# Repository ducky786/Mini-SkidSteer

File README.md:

# DESK TOP SKIDSTEER

My project is a small RC skidsteer for the desktop to cure bordom. This Skidsteer is around 80mm x 70mm with a arm that includes a bucket tilt. The arm and the Tilt are powered by servos while the drive bace is powered by 2 N20 motors. The 
I wanted to build this beucase I found an intrest in these small desktop toys that could be fun to kill time on your desk. I went for a skidsteer because it would consist of something more then just simply driving around on top of your desk.  Like picking up small
things and throwing them around. Another reason I wanted to build this was beucase I also wanted to learn something new! During this build I have defenetly learn a significant amound of cad and PCB design! But the main reason is to have pure fun with a mini constuction vehicel!! 
# CAD:

The wheels are place holders for a 26mm D-ring Wheels: [Wheels](https://www.amazon.com/10pcs-D-Hole-Rubber-Wheel-Suitable/dp/B0DHS12GDV/ref=sr_1_3?crid=JYD2UDDS1NEK&dib=eyJ2IjoiMSJ9.ZUXECa4swdUpnlJCNFAChQdrSCF2_hyKX8ZRQ2ua2YUncgO5PiK5-fhxESZpHSc04xRms3dZP7bGo22MBXnhl2GiFjDrSeCp869mCpt2dDXZk3buzny7Sudp0jAhjKUcEA7j7tARDvNgPD-RxQ5BFpu_E_WtRcR4WOEt8GHUK6RN7SL4UtHEZsm3R7V5XJPagJUR_B_1uT-b5DjtV5n_0yKpyzRRbffM9ZdXg7WJBNcLcRB7_FF1wIvSGdpv8AstDdXbFSEhfm7NKxJSys81x3GqS7OE68Zp1z-JxQ1wk4M.ZB2Gj1L4j-ghlaeTYDEn---1bgTsKAoD6mUg0iyUQDg&dib_tag=se&keywords=n20+motor+wheels&qid=1753996532&sprefix=n20+motor+wheels%2Caps%2C124&sr=8-3)

# PCB:

# Wire-ring Diagram:

# FIRMWARE:

# BOM:

| Part              | Quantity        | Price  | Link                                                                                                                                                                                                                                                                                                                                                                                                                                                                                                                                                                                             |
|-------------------|-----------------|--------|--------------------------------------------------------------------------------------------------------------------------------------------------------------------------------------------------------------------------------------------------------------------------------------------------------------------------------------------------------------------------------------------------------------------------------------------------------------------------------------------------------------------------------------------------------------------------------------------------|
| N20 Motors        | 2(comes with 3) | $9.99  | https://www.amazon.com/Acxico-Micro-Motor-3V-6V-Gearbox/dp/B09DG3GCGK/ref=sr_1_6?crid=2OI8KQ857NSB1&dib=eyJ2IjoiMSJ9.PkC4L7juc7TBvok5GyDdI7hLUVsyJ1bXnRvRXlihFuC0tuFr0EGfKIyFzPnAN5yKceG9SoHprCtbqYV4n7I_Zr-v1A3x4khd6QiGyFw154ci5AssINA13NQLaWW2FqRzkFSk5cMwQ_EzwAtZCdI4P1ZcjGlnBcWYDLRE6otBmBDZr-u-BCU8r-wDdhpqUWX1Tu8i0kttiPHRSya24dCC48jhBziSzb0c3fjVY09DPHAQZ82jpYmAuD5ZZlAhsl23H0OCtbkOdgwN9skI81BPHVLWugW-Nfu1aNeGGhEbY2A.YVqZWv7cAqLJMA5_e4uScZz4QUkldOzOEJFcsFCGGJc&dib_tag=se&keywords=N20+motors&qid=1753995893&sprefix=n20+motors%2Caps%2C137&sr=8-6                                 |
| Buck Converter    | 1               | $1.33  | https://www.aliexpress.us/item/3256809224651081.html?spm=a2g0o.productlist.main.4.51657788dJtPVx&aem_p4p_detail=202507291440413645293400774410000784233&algo_pvid=df29eea6-074c-4400-bbc7-bf50f68b366f&algo_exp_id=df29eea6-074c-4400-bbc7-bf50f68b366f-3&pdp_ext_f=%7B%22order%22%3A%228%22%2C%22eval%22%3A%221%22%7D&pdp_npi=4%40dis%21USD%211.33%210.77%21%21%211.33%210.77%21%402103245417538252412368642e00ae%2112000049015556004%21sea%21US%216238534509%21X&curPageLogUid=JzbwaxZXZo7C&utparam-url=scene%3Asearch%7Cquery_from%3A&search_p4p_id=202507291440413645293400774410000784233_1 |
| DRV8833           | 1               | $2.24  | https://www.aliexpress.us/item/3256806906685301.html?spm=a2g0o.productlist.main.4.6ea27fc4uwtPAg&aem_p4p_detail=2025073114100314644857276615300003037063&algo_pvid=8cc3c05c-6c7b-45dc-bfae-e0f3d2b46d45&algo_exp_id=8cc3c05c-6c7b-45dc-bfae-e0f3d2b46d45-3&pdp_ext_f=%7B"order"%3A"12"%2C"eval"%3A"1"%7D&pdp_npi=4%40dis%21USD%215.74%212.24%21%21%2141.08%2116.03%21%402103244617539962038712743e4150%2112000039378712005%21sea%21US%216395794669%21X&curPageLogUid=tkZwLZppvI4E&utparam-url=scene%3Asearch%7Cquery_from%3A&search_p4p_id=2025073114100314644857276615300003037063_2            |
| Servos sg90       | 2               | $3.98  | https://www.aliexpress.us/item/3256805909602108.html?spm=a2g0o.productlist.main.1.4363B3dwB3dwVh&aem_p4p_detail=20250731141230268300773175950003082043&algo_pvid=4fc0f702-53c1-41f5-beab-abc79d099066&algo_exp_id=4fc0f702-53c1-41f5-beab-abc79d099066-0&pdp_ext_f=%7B"order"%3A"42"%2C"eval"%3A"1"%7D&pdp_npi=4%40dis%21USD%211.99%211.99%21%21%2114.27%2114.27%21%402103244817539963500562681e2fa1%2112000035720830774%21sea%21US%216395794669%21X&curPageLogUid=MTCLJAN4xnVc&utparam-url=scene%3Asearch%7Cquery_from%3A&search_p4p_id=20250731141230268300773175950003082043_1                |
| Wheels            | 4(comes in 10)  | $6.73  | https://www.amazon.com/10pcs-D-Hole-Rubber-Wheel-Suitable/dp/B0DHS12GDV/ref=sr_1_3?crid=JYD2UDDS1NEK&dib=eyJ2IjoiMSJ9.ZUXECa4swdUpnlJCNFAChQdrSCF2_hyKX8ZRQ2ua2YUncgO5PiK5-fhxESZpHSc04xRms3dZP7bGo22MBXnhl2GiFjDrSeCp869mCpt2dDXZk3buzny7Sudp0jAhjKUcEA7j7tARDvNgPD-RxQ5BFpu_E_WtRcR4WOEt8GHUK6RN7SL4UtHEZsm3R7V5XJPagJUR_B_1uT-b5DjtV5n_0yKpyzRRbffM9ZdXg7WJBNcLcRB7_FF1wIvSGdpv8AstDdXbFSEhfm7NKxJSys81x3GqS7OE68Zp1z-JxQ1wk4M.ZB2Gj1L4j-ghlaeTYDEn---1bgTsKAoD6mUg0iyUQDg&dib_tag=se&keywords=n20+motor+wheels&qid=1753996532&sprefix=n20+motor+wheels%2Caps%2C124&sr=8-3                    |
| Xiao ESP-32       | 1               | $4.43  | https://www.aliexpress.us/item/3256806898073871.html?spm=a2g0o.productlist.main.1.6ed9192cMtXvMa&aem_p4p_detail=202507311418121917005778551220003052960&algo_pvid=a3b60e4a-0d34-4bf9-a8ab-66c9a24a1449&algo_exp_id=a3b60e4a-0d34-4bf9-a8ab-66c9a24a1449-0&pdp_ext_f=%7B"order"%3A"667"%2C"eval"%3A"1"%7D&pdp_npi=4%40dis%21USD%217.93%214.43%21%21%2156.74%2131.69%21%402103246617539966920224373e09d8%2112000039345574623%21sea%21US%216395794669%21X&curPageLogUid=fVxbMNHtmWwP&utparam-url=scene%3Asearch%7Cquery_from%3A&search_p4p_id=202507311418121917005778551220003052960_1             |
| XT30              | 1               | $1.99  | https://www.aliexpress.us/item/3256808022842675.html?spm=a2g0o.productlist.main.13.4d341f017djqKR&aem_p4p_detail=202507311421295032891313211630003124381&algo_pvid=09ceb7e3-6a2c-4cd8-b174-e051d28f31cf&algo_exp_id=09ceb7e3-6a2c-4cd8-b174-e051d28f31cf-12&pdp_ext_f=%7B"order"%3A"868"%2C"eval"%3A"1"%7D&pdp_npi=4%40dis%21USD%213.36%211.99%21%21%2124.07%2114.26%21%402101ea8c17539968895486921e633c%2112000044241722915%21sea%21US%216395794669%21X&curPageLogUid=UwLOdHYcZP7Q&utparam-url=scene%3Asearch%7Cquery_from%3A&search_p4p_id=202507311421295032891313211630003124381_5           |
| Pin Headers       | 1               | $2.79  | https://www.aliexpress.us/item/3256805730789728.html?spm=a2g0o.productlist.main.4.411940cd8jqG2L&aem_p4p_detail=202507311422337454539819102040003087391&algo_pvid=d1d8e6eb-01b7-4f35-8242-8ff7e607a94f&algo_exp_id=d1d8e6eb-01b7-4f35-8242-8ff7e607a94f-3&pdp_ext_f=%7B"order"%3A"45"%2C"eval"%3A"1"%7D&pdp_npi=4%40dis%21USD%212.97%212.79%21%21%2121.23%2119.96%21%402101c80217539969536874429edd11%2112000034840648426%21sea%21US%216395794669%21X&curPageLogUid=ouSfWTDoT1n5&utparam-url=scene%3Asearch%7Cquery_from%3A&search_p4p_id=202507311422337454539819102040003087391_2              |
| Female Header     | 1               | $0.72  | https://www.aliexpress.us/item/2251832677159829.html?spm=a2g0o.productlist.main.2.4c5d2d450nHIIb&algo_pvid=d4a0da79-7db8-49c6-9d13-7a283dafbbd1&algo_exp_id=d4a0da79-7db8-49c6-9d13-7a283dafbbd1-1&pdp_ext_f=%7B"order"%3A"5"%2C"eval"%3A"1"%7D&pdp_npi=4%40dis%21USD%210.76%210.72%21%21%210.76%210.72%21%402101c5bf17539970477882420ed5c5%2165355679105%21sea%21US%216395794669%21X&curPageLogUid=lampIYBHwC27&utparam-url=scene%3Asearch%7Cquery_from%3A                                                                                                                                      |
| Screw Terminal    | 1               | $3.24  | https://www.aliexpress.us/item/3256804481581777.html?spm=a2g0o.productlist.main.1.194342a3snY3aE&aem_p4p_detail=2025073114253012899010225579360003107920&algo_pvid=96e8f427-5b18-470a-8388-f4d98a1d7e28&algo_exp_id=96e8f427-5b18-470a-8388-f4d98a1d7e28-0&pdp_ext_f=%7B"order"%3A"238"%2C"eval"%3A"1"%7D&pdp_npi=4%40dis%21USD%212.84%211.99%21%21%212.84%211.99%21%402101c59817539971308151068e26ea%2112000030040613013%21sea%21US%216395794669%21X&curPageLogUid=c4xiFsyJKPl5&utparam-url=scene%3Asearch%7Cquery_from%3A&search_p4p_id=2025073114253012899010225579360003107920_1             |
| TATTU lipo        | 1               | $15.99 | Amazon.com: Gens ace 7.4V 450mAh 2S LiPo Battery Pack 25C/50C with JST Plug for Emax Babyhawk RC Heli 250 Helicopter Small Airplane Micro FPV Racing Drone Quadcopter : Toys & Games                                                                                                                                                                                                                                                                                                                                                                                                             |
| Motor Mount       | 2               | $6.49  | https://www.amazon.com/MECCANIXITY-Mounting-Bracket-11-5mm-Screws/dp/B09NN6FQ78/ref=sr_1_3?crid=3MVOGE46GNN04&dib=eyJ2IjoiMSJ9.7mrWQi7UXqMV7C8DaatAef39dP0G71RFsuPEG_XQyZKKUwQQHNfWP72EzPdgqQ6W5rUopt4tlHvO017cmHnm03FdxsItOalGfAwNVxY3bojMNwevN9EQyjcX-VgJt0J2w3oODTu0YaNwuXxELHLnAOeQSJFFpWg2ScGQGenvYxxZ44uSi_ixXSxDr3VX3fX4k0X6RNWheNJeRjMrWZN_lZZkrp-MG0c3iGA-q40ouAc.O8g6XJyt18RVRM3cLohr8Bw2el-1G1WwcM1bjLhDAoQ&dib_tag=se&keywords=n20+motor+mount&qid=1754008952&sprefix=n20+motor+mount%2Caps%2C162&sr=8-3                                                                             |
| 3D Print Shipping |                 | ~$10   |                                                                                                                                                                                                                                                                                                                                                                                                                                                                                                                                                                                                  |
| PCB               | 1               | ~$15   |                                                                                                                                                                                                                                                                                                                                                                                                                                                                                                                                                                                                  |
| TOTAL             |                 | 79.92  |                                                                                                                                                                                                                                                                                                                                                                                                                                                                                                                                                                                                  |

# FINAL PRODUCT:

This is the final PCB design! I feel that it came out Great and what I love about this PCB is that I can remove it from the Skidsteer and place it into a 3d printed car! I plan on using this it on other projects.

Now the skidseer interms of CAD, it came out great too. There defenety have been some bad tolerences and alignment but it came together well enough.

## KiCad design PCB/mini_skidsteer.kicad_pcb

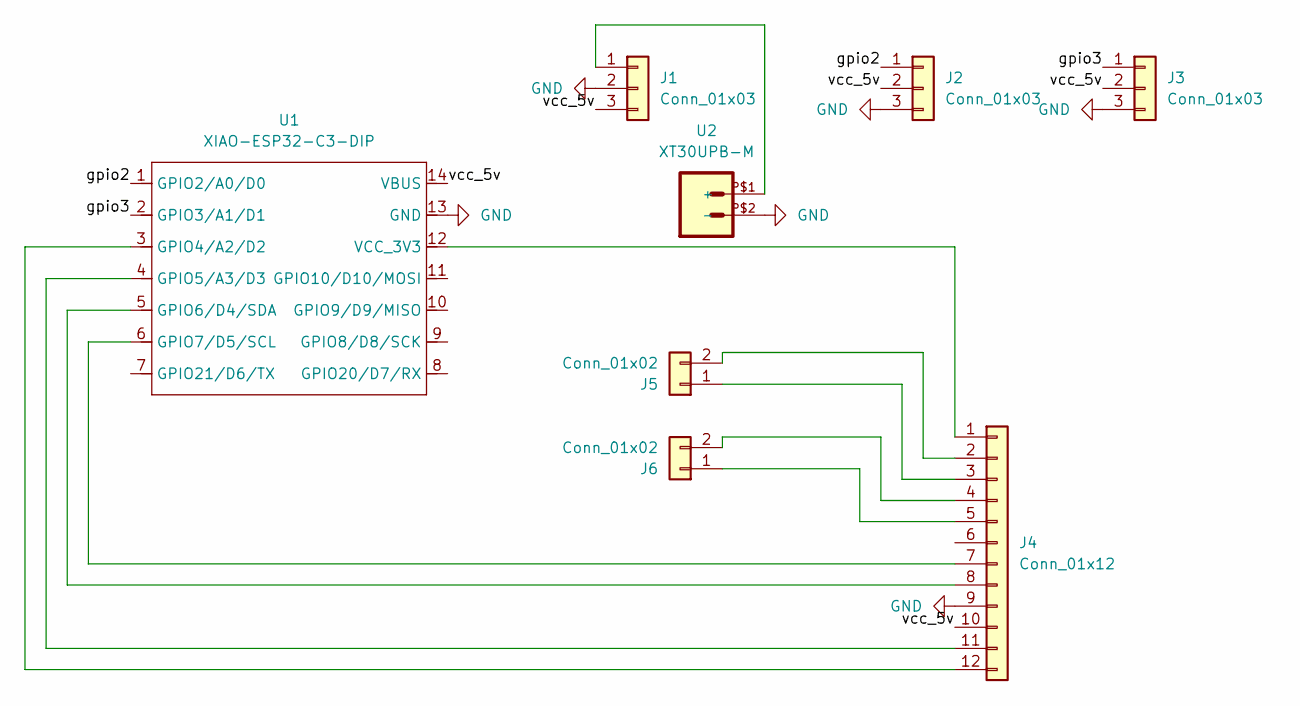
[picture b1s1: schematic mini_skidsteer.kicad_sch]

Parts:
J1: Conn_01x03; PinSocket_1x03_P2.54mm_Vertical
J2, J3: Conn_01x03; PinHeader_1x03_P2.54mm_Vertical
J4: Conn_01x12; drv8833
J5, J6: Conn_01x02; Altech_AK300_1x02_P5.00mm_45-Degree
U1: XIAO-ESP32-C3-DIP; XIAO-ESP32C3-DIP
U2: XT30UPB-M

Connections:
/gpio2: J2.1, U1.1 (GPIO2/A0/D0)
/gpio3: J3.1, U1.2 (GPIO3/A1/D1)
/vcc_5v: J1.3, J2.2, J3.2, J4.10, U1.14 (VBUS)
GND: J1.2, J2.3, J3.3, J4.9, U1.13 (GND), U2.P$2 (-)
unnamed: J1.1, U2.P$1 (+)
unnamed: J4.1, U1.12 (VCC_3V3)
unnamed: J4.2, J5.2
unnamed: J4.3, J5.1
unnamed: J4.4, J6.2
unnamed: J4.5, J6.1
unnamed: J4.7, U1.6 (GPIO7/D5/SCL)
unnamed: J4.8, U1.5 (GPIO6/D4/SDA)
unnamed: J4.11, U1.4 (GPIO5/A3/D3)
unnamed: J4.12, U1.3 (GPIO4/A2/D2)

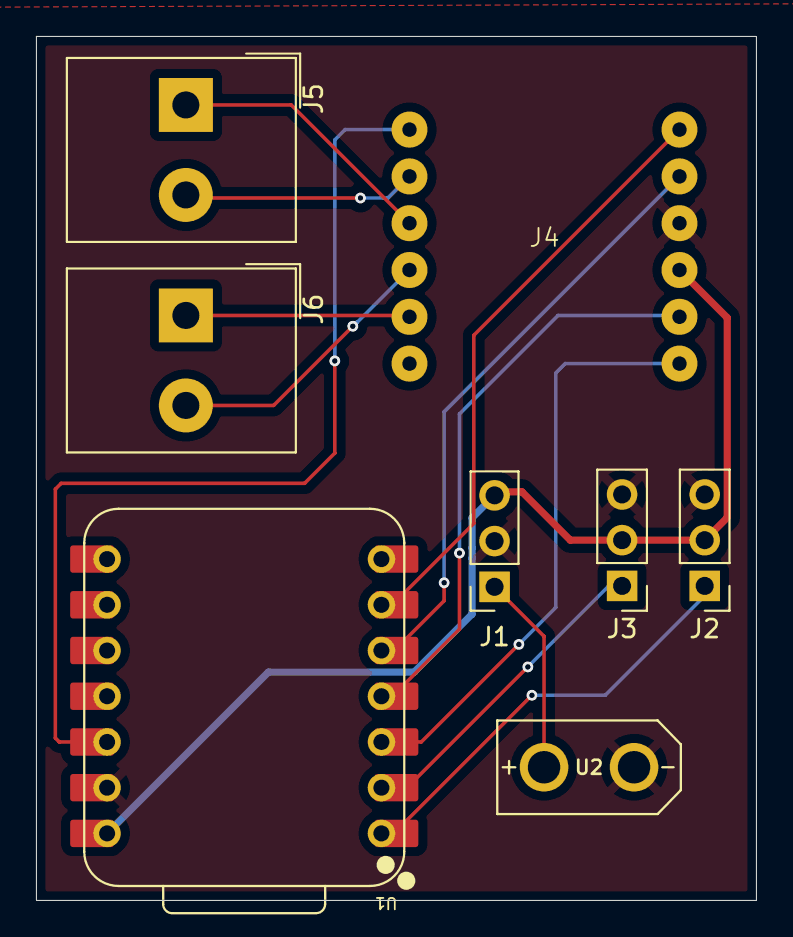
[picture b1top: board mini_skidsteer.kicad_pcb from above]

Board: 2 copper layers, 40.0 x 48.0 mm, 8 parts (0 on the bottom side), 14 nets.

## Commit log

2025-08-01 Create s
2025-08-01 Create n
2025-08-01 Create a
2025-08-01 Create c
2025-10-26 Added controller
2025-10-26 added stuff
